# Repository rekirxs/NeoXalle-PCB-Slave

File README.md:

# NeoXalle-PCB-Slave

A full PCB work for a sport sensorial reaction device called NeoXalle.

Similar products exist in the market such as BlazePod and Fitlight, based on this projects but with upgrades for the better.

NeoXalle is a sport training device made up of 4 pods with LEDS, accelerometers, vibratiion motors and speaker to simulate a training for a variety of sports, all controlled thru an mobile APP where the user has the full control of the pods and can direct the training at any tipe of likings.

The purpose of this pcb is to transform the actual circuit wired phisically into a pcb more compact and more capable than the already existing one.

**Overview**

This repository contains the design files and the images of each part.

### [Watch this video on YouTube](https://youtu.be/leAVq9ZJ1fE)
**Screenshots**

CSV FOUND AS FILE AS WELL

|Item                        |Description                        |Quantity|Unit Price ($)|Total Price ($)|URL                                                 |Running Total|
|----------------------------|-----------------------------------|--------|--------------|---------------|----------------------------------------------------|-------------|
|ESP32-C3 WROOOM 02u         |Microcontroller                    |5       |1.785         |19.00          |https://es.aliexpress.com/item/1005004386637738.html|19.00        |
|ADXL375                     |Acelerometer                       |5       |7.2           |36.0           |https://es.aliexpress.com/item/1005011998515044.html|55.00        |
|BQ25895RTW                  |Battery Charger IC                 |5       |1.73          |8.65           |https://es.aliexpress.com/item/1005007164079601.html|63.65        |
|PCB                         |PCB                                |5       |7.2           |36             |https://cart.jlcpcb.com/shopcart/cart/              |99.65        |

**Repository layout**

- `pcb/` — KiCad schematic and PCB files-
- `images/` — project screenshots used by this README

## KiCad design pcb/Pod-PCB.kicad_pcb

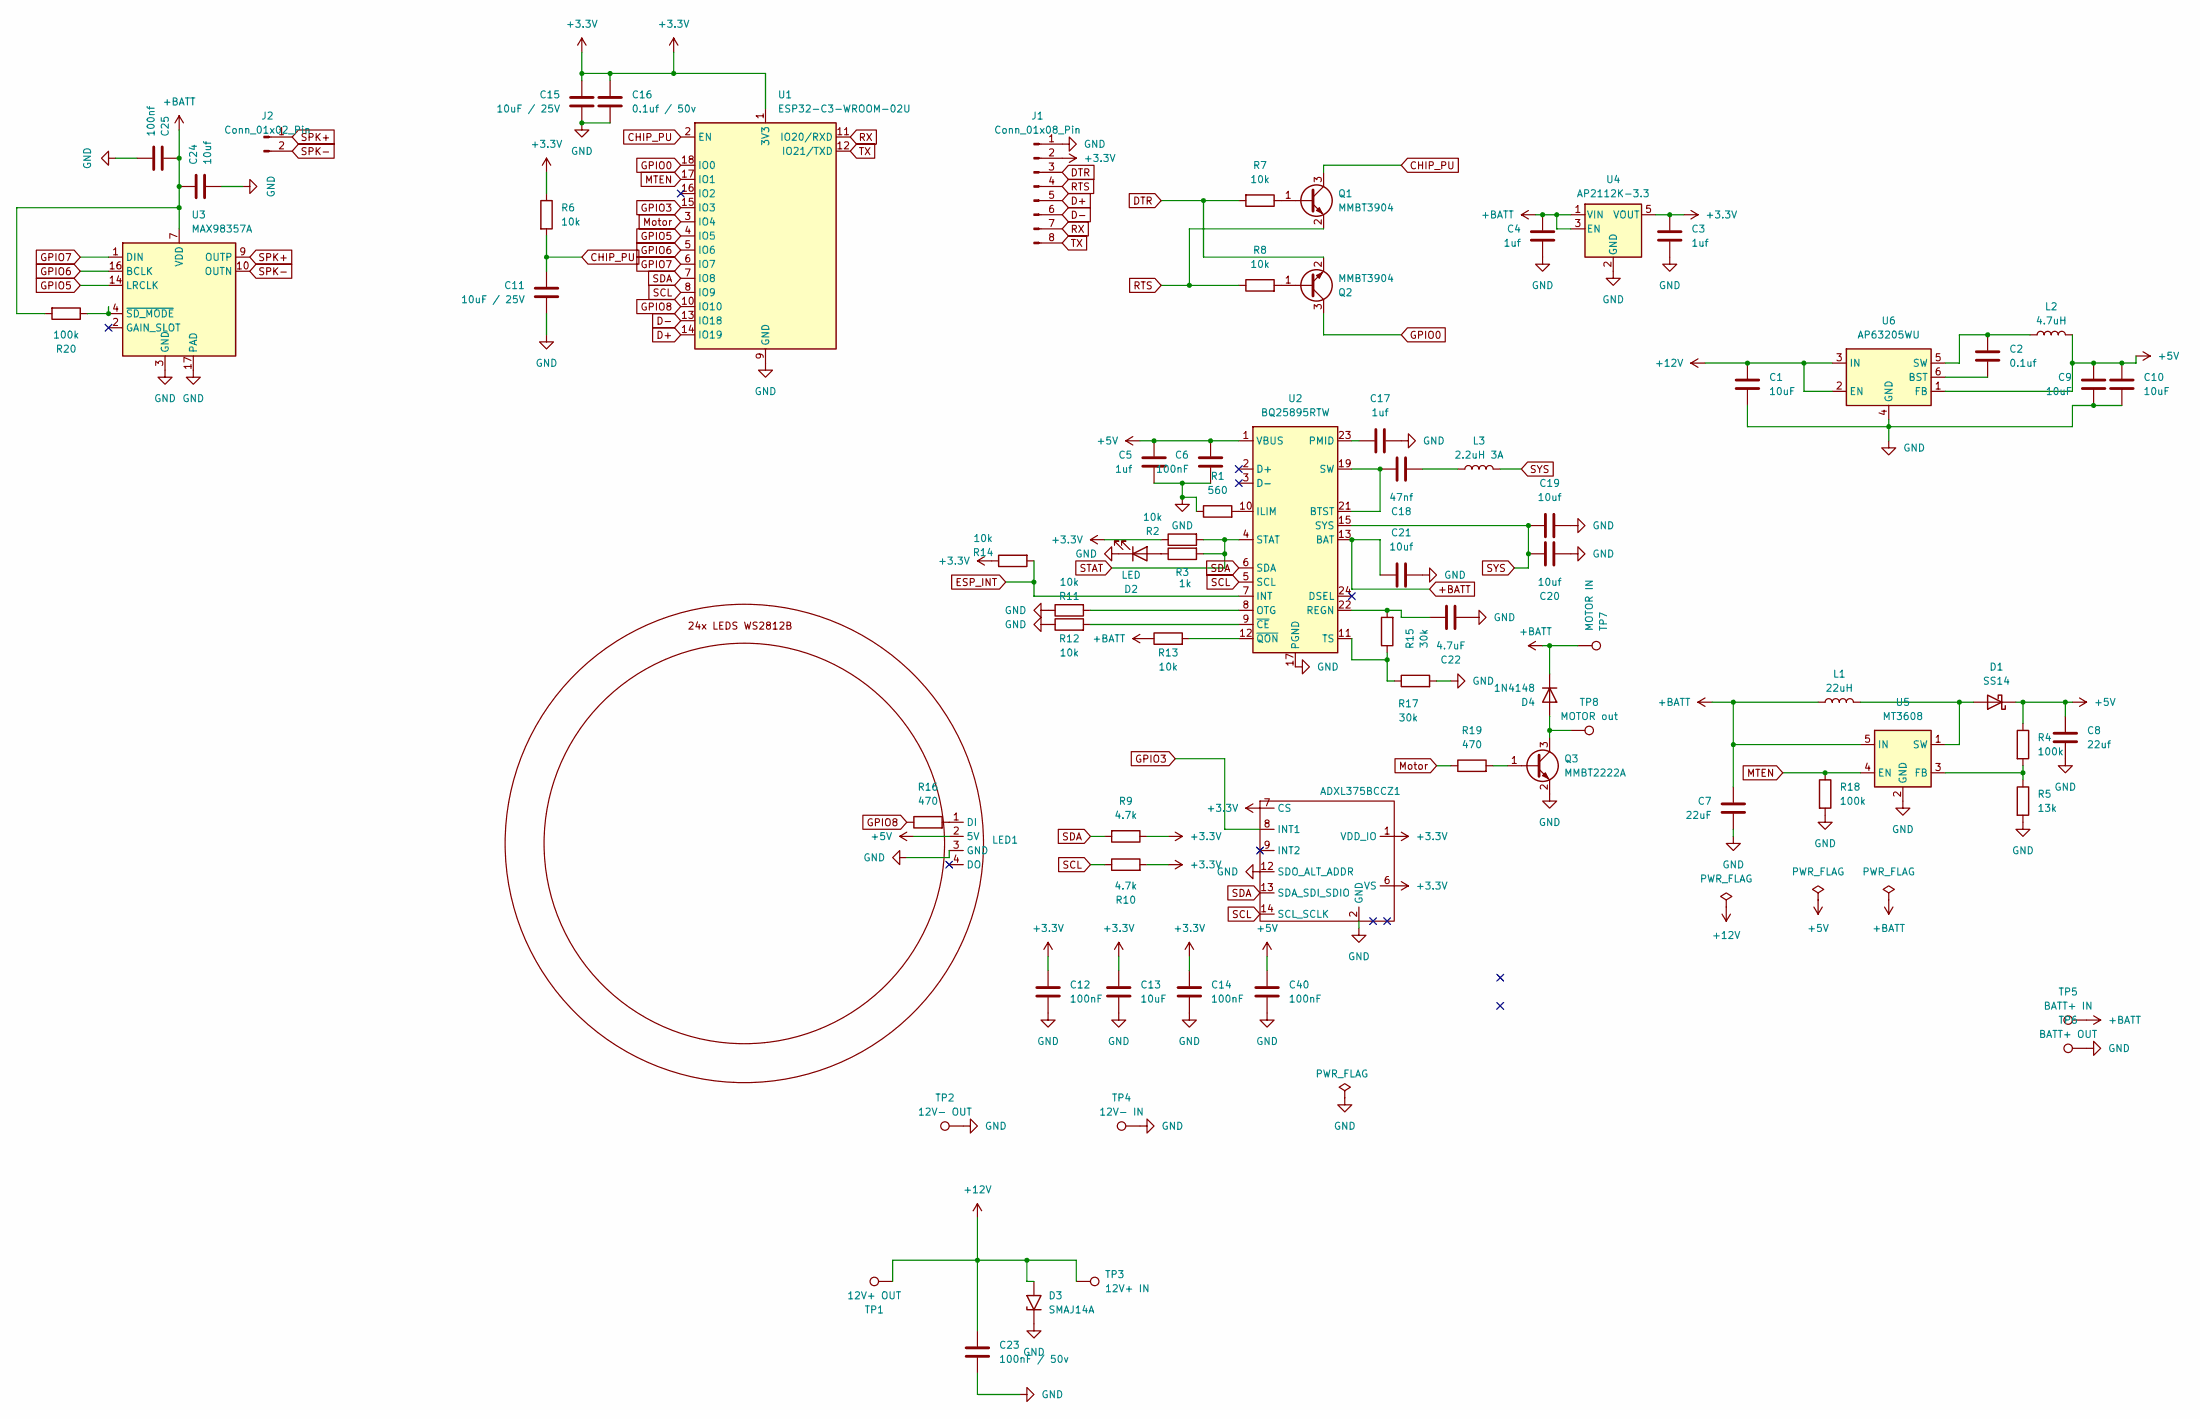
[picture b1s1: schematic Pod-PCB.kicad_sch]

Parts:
ADXL375BCCZ1: PQFN80P500X300X100-14N
C1, C9, C10, C13: 10uF; C_1206_3216Metric
C2: 0.1uf; C_0805_2012Metric
C3, C4, C5, C17: 1uf; C_0805_2012Metric
C6, C12, C14, C40: 100nF; C_0805_2012Metric
C7: 22uF; C_1206_3216Metric
C8: 22uf; C_1206_3216Metric
C11, C15: 10uF / 25V; C_1206_3216Metric
C16: 0.1uf / 50v; C_0805_2012Metric
C18: 47nf; C_0805_2012Metric
C19, C20, C21, C24: 10uf; C_1206_3216Metric
C22: 4.7uF; C_0805_2012Metric
C23: 100nF / 50v; C_0805_2012Metric
C25: 100nf; C_0805_2012Metric
D1: SS14; D_SMA
D2: LED; LED_0805_2012Metric
D3: SMAJ14A; D_SMA
D4: 1N4148; D_DO-35_SOD27_P7.62mm_Horizontal
J1: Conn_01x08_Pin; PinHeader_1x08_P2.54mm_Vertical
J2: Conn_01x02_Pin; PinHeader_1x02_P2.54mm_Vertical
L1: 22uH; L_1210_3225Metric
L2: 4.7uH; L_1210_3225Metric
L3: 2.2uH 3A; L_1812_4532Metric
LED1: Untitled
Q1, Q2: MMBT3904; SOT-23
Q3: MMBT2222A; SOT-23
R1: 560; R_0805_2012Metric
R2, R6, R7, R8, R11, R12, R13, R14: 10k; R_0805_2012Metric
R3: 1k; R_0805_2012Metric
R4, R18, R20: 100k; R_0805_2012Metric
R5: 13k; R_0805_2012Metric
R9, R10: 4.7k; R_0805_2012Metric
R15, R17: 30k; R_0805_2012Metric
R16, R19: 470; R_0805_2012Metric
TP1: 12V+ OUT; TestPoint_THTPad_D3.0mm_Drill1.5mm
TP2: 12V- OUT; TestPoint_THTPad_D3.0mm_Drill1.5mm
TP3: 12V+ IN; TestPoint_THTPad_D3.0mm_Drill1.5mm
TP4: 12V- IN; TestPoint_THTPad_D3.0mm_Drill1.5mm
TP5: BATT+ IN; TestPoint_THTPad_D3.0mm_Drill1.5mm
TP6: BATT+ OUT; TestPoint_THTPad_D3.0mm_Drill1.5mm
TP7: MOTOR IN; TestPoint_THTPad_D3.0mm_Drill1.5mm
TP8: MOTOR out; TestPoint_THTPad_D3.0mm_Drill1.5mm
U1: ESP32-C3-WROOM-02U
U2: BQ25895RTW; Texas_RTW_WQFN-24-1EP_4x4mm_P0.5mm_EP2.7x2.7mm_ThermalVias
U3: MAX98357A; TQFN-16-1EP_3x3mm_P0.5mm_EP1.23x1.23mm
U4: AP2112K-3.3; SOT-23-5
U5: MT3608; SOT-23-6
U6: AP63205WU; TSOT-23-6

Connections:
+3.3V: ADXL375BCCZ1.1 (VDD_IO), ADXL375BCCZ1.6 (VS), ADXL375BCCZ1.7 (CS), C3.1, C12.1, C13.1, C14.1, C15.1, C16.1, J1.2, R2.1, R6.1, R9.1, R10.2, R14.1, U1.1 (3V3), U4.5 (VOUT)
+5V: C5.1, C6.1, C8.1, C9.1, C10.1, C40.1, D1.1 (K), L2.2, LED1.2 (5V), R4.1, U2.1 (VBUS), U6.1 (FB)
+12V: C1.1, C23.1, D3.2 (A2), TP1.1, TP3.1, U6.2 (EN), U6.3 (IN)
+BATT: C4.1, C7.1, C21.1, C24.1, C25.1, D4.1 (K), L1.2, R13.1, R20.2, TP5.1, TP7.1, U2.13 (BAT), U2.14 (BAT), U3.7 (VDD), U3.8 (VDD), U4.1 (VIN), U4.3 (EN), U5.5 (IN)
CHIP_PU: C11.1, Q1.3 (C), R6.2, U1.2 (EN)
D+: J1.5, U1.14 (IO19)
D-: J1.6, U1.13 (IO18)
DTR: J1.3, Q2.2 (E), R7.2
ESP_INT: R14.2, U2.7 (INT)
GND: ADXL375BCCZ1.2 (GND), ADXL375BCCZ1.12 (SDO_ALT_ADDR), C1.2, C3.2, C4.2, C5.2, C6.2, C7.2, C8.2, C9.2, C10.2, C11.2, C12.2, C13.2, C14.2, C15.2, C16.2, C17.2, C19.2, C20.1, C21.2, C22.1, C23.2, C24.2, C25.2, C40.2, D2.1 (K), D3.1 (A1), J1.1, LED1.3 (GND), Q3.2 (E), R1.1, R5.2, R11.1, R12.1, R17.2, R18.2, TP2.1, TP4.1, TP6.1, U1.9 (GND), U1.19 (GND), U2.17 (PGND), U2.18 (PGND), U2.25 (PGND), U3.3 (GND), U3.11 (GND), U3.15 (GND), U3.17 (PAD), U4.2 (GND), U5.2 (GND), U6.4 (GND); also elsewhere on the board
GPIO0: Q2.3 (C), U1.18 (IO0)
GPIO3: ADXL375BCCZ1.8 (INT1), U1.15 (IO3)
GPIO5: U1.4 (IO5), U3.14 (LRCLK)
GPIO6: U1.5 (IO6), U3.16 (BCLK)
GPIO7: U1.6 (IO7), U3.1 (DIN)
GPIO8: R16.1, U1.10 (IO10)
MTEN: R18.1, U1.17 (IO1), U5.4 (EN)
Motor: R19.1, U1.3 (IO4)
unnamed 18: C18.2, L3.1; also elsewhere on the board
unnamed: D1.2 (A), L1.1, U5.1 (SW)
unnamed: D2.2 (A), R3.1
unnamed: D4.2 (A), Q3.3 (C), TP8.1
unnamed: LED1.1 (DI), R16.2
unnamed: Q1.1 (B), R7.1
unnamed: Q2.1 (B), R8.2
unnamed: Q3.1 (B), R19.2
unnamed 26: C18.1, U2.19 (SW), U2.20 (SW), U2.21 (BTST); also elsewhere on the board
unnamed: R1.2, U2.10 (ILIM)
unnamed: R11.2, U2.8 (OTG)
unnamed 29: C17.1, U2.23 (PMID); also elsewhere on the board
unnamed: C22.2, R15.2, U2.22 (REGN)
unnamed: R15.1, R17.1, U2.11 (TS)
unnamed: R12.2, U2.9 (~CE)
unnamed: R13.2, U2.12 (~QON)
unnamed: R20.1, U3.4 (~SD_MODE)
unnamed: R4.2, R5.1, U5.3 (FB)
unnamed: C2.2, U6.6 (BST)
unnamed: C2.1, L2.1, U6.5 (SW)
RTS: J1.4, Q1.2 (E), R8.1
RX: J1.7, U1.11 (IO20/RXD)
SCL: ADXL375BCCZ1.14 (SCL_SCLK), R10.1, U1.8 (IO9), U2.5 (SCL)
SDA: ADXL375BCCZ1.13 (SDA_SDI_SDIO), R9.2, U1.7 (IO8), U2.6 (SDA)
SPK+: J2.1, U3.9 (OUTP)
SPK-: J2.2, U3.10 (OUTN)
STAT: R2.2, R3.2, U2.4 (STAT)
SYS: C19.1, C20.2, L3.2, U2.15 (SYS), U2.16 (SYS)
TX: J1.8, U1.12 (IO21/TXD)

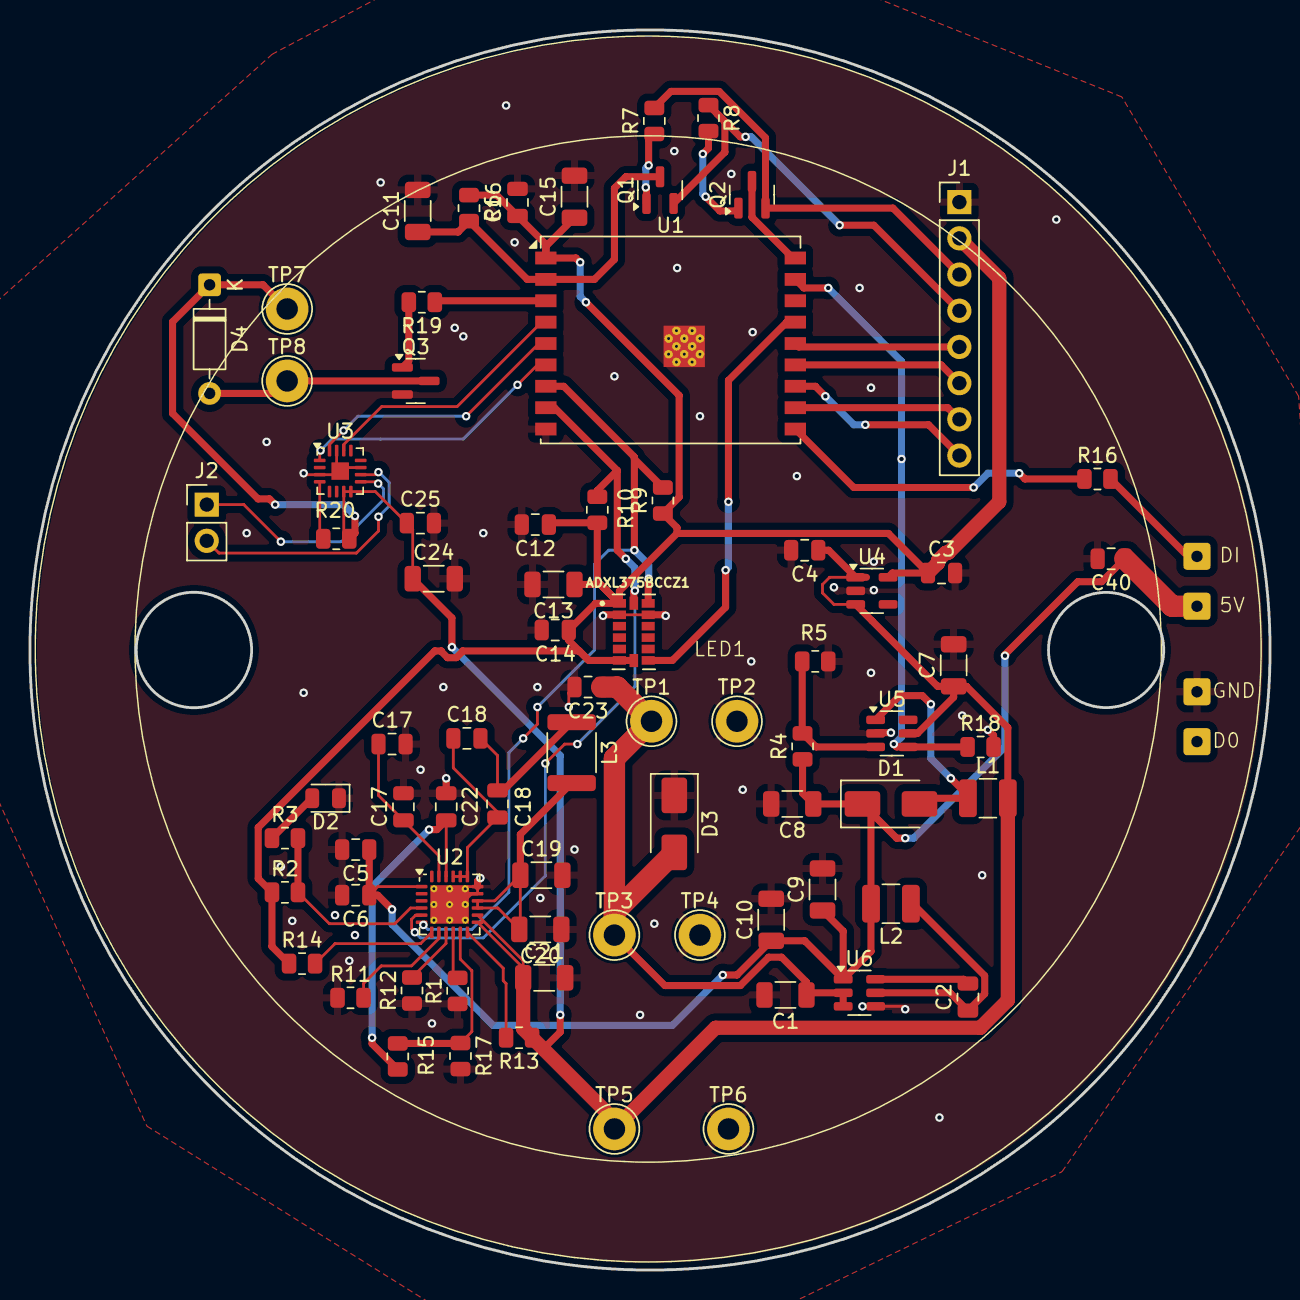
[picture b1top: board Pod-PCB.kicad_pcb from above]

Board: 2 copper layers, 87.0 x 87.0 mm, 76 parts (0 on the bottom side), 47 nets.

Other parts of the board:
C17#2: 1uf; C_0805_2012Metric
C18#2: 47nf; C_0805_2012Metric

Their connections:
GND: C17#2.2; also elsewhere on the board
unnamed 18: C18#2.2; also elsewhere on the board
unnamed 26: C18#2.1; also elsewhere on the board
unnamed 29: C17#2.1; also elsewhere on the board

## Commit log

2026-06-16 Create a
2026-06-16 Rename imagen_2026-06-16_170911330.png to 3d.png
2026-06-16 Rename imagen_2026-06-16_170958310.png to pcb.png
2026-06-16 Rename imagen_2026-06-16_171010144.png to schematic.png
